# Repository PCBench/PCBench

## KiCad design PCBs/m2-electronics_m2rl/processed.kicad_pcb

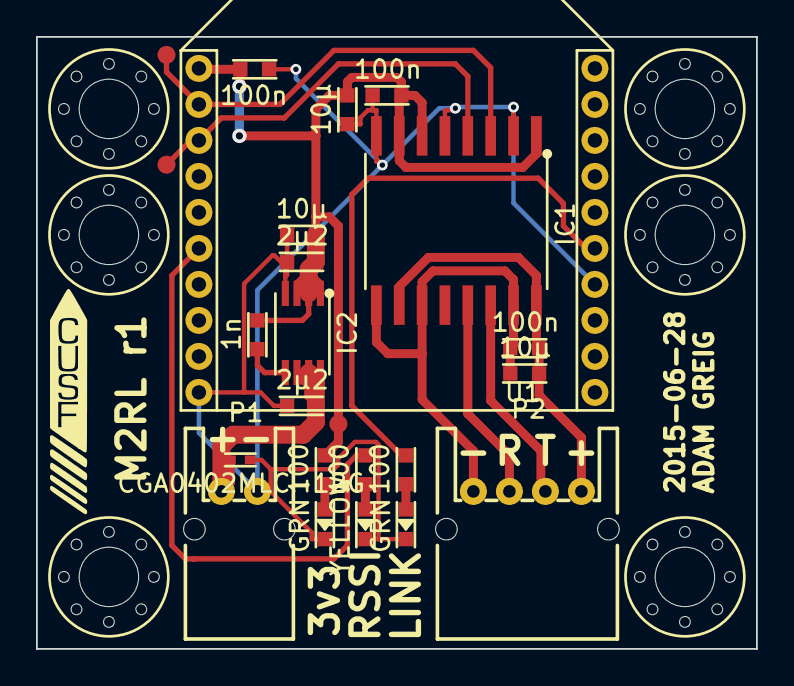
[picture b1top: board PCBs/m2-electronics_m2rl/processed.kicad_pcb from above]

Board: 2 copper layers, 40.0 x 34.0 mm, 30 parts (0 on the bottom side), 15 nets.

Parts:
C1, C7, C9: 10µ; C0603
C2, C3, C5: 100n; C0603
C4, C8: 2µ2; C0603
C6: 1n; C0603
D1: YELLOW; LED0603
D2: CGA0402MLC-12G; R0402
D3, D4: GRN; LED0603
IC1: ADuM5201; SOIC16W
IC2: ADP3335; MSOP8
M3_MOUNT, M3_MOUNT_2, M3_MOUNT_3, M3_MOUNT_4, M3_MOUNT_5, M3_MOUNT_6: VAL**; M3_MOUNT
P1: CONN_01X02; S02B-PASK-2
P2: CONN_01X04; S04B-PASK-2
R1, R2, R3: 100; R0603
TP3, TP4, TP5: TESTPAD
U1: XBEE

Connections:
+3V3: C1.1, C2.1, C3.1, C6.1, C8.1, C9.1, IC1.1, IC1.6, IC1.7, IC2.1, IC2.2, IC2.3, R3.1, TP5.1, U1.1
/DIN: IC1.4, TP4.1, U1.3
/DOUT: IC1.3, TP3.1, U1.2
GND: C1.2, C2.2, C3.2, C4.2, C8.2, C9.2, D1.1, D2.2, D3.1, D4.1, IC1.2, IC1.5, IC1.8, IC2.4, P1.1, U1.10, U1.14
unnamed: C4.1, D2.1, IC2.6, IC2.7, IC2.8, P1.2
unnamed: C5.1, C7.1, IC1.10, IC1.16, P2.1
unnamed: C5.2, C7.2, IC1.9, IC1.11, IC1.15, P2.4
unnamed: C6.2, IC2.5
unnamed: D1.2, R1.2
unnamed: D3.2, R2.2
unnamed: D4.2, R3.2
unnamed: IC1.13, P2.3
unnamed: IC1.14, P2.2
unnamed: R1.1, U1.6
unnamed: R2.1, U1.15

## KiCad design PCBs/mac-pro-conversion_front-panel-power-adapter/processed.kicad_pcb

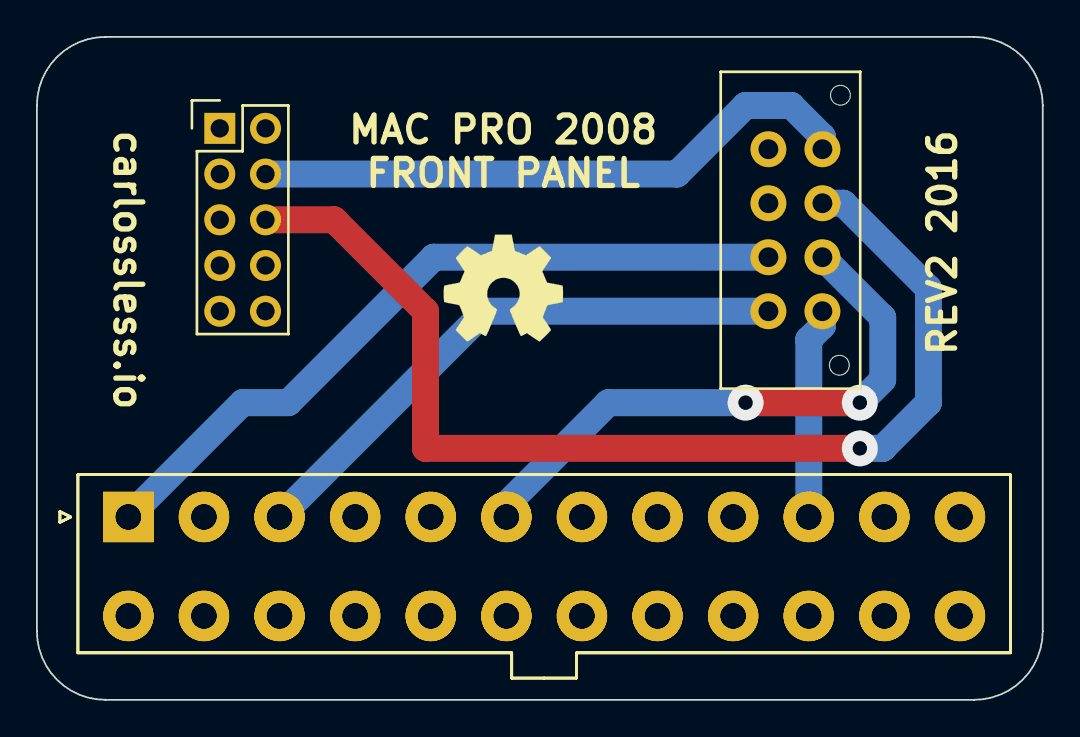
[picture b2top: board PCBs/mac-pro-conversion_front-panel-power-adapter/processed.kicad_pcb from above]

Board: 2 copper layers, 55.9 x 36.8 mm, 4 parts (0 on the bottom side), 26 nets.

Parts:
P3: CONN_02X04; Molex_Microfit3_Header_02x04_Straight_43045-0828
P4: CONN_02X05; Pin_Header_Straight_2x05
P7, P8: CONN_02X12; Molex_MiniFit-JR-5556-24A_2x12x4.20mm_Straight

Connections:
ATX01_3.3V: P3.2, P7.1, P8.1
ATX02: P7.2, P8.2
ATX04: P7.4, P8.4
ATX06_5V: P3.6, P7.6, P8.6
ATX08: P7.8, P8.8
ATX10_12V: P3.5, P7.10, P8.10
ATX12: P7.12, P8.12
ATX14: P7.14, P8.14
ATX16: P7.16, P8.16
ATX18: P7.18, P8.18
ATX20: P7.20, P8.20
ATX22: P7.22, P8.22
ATX24: P7.24, P8.24
ATX_05: P7.5, P8.5
ATX_07: P7.7, P8.7
ATX_09: P7.9, P8.9
ATX_11: P7.11, P8.11
ATX_13: P7.13, P8.13
ATX_15: P7.15, P8.15
ATX_17: P7.17, P8.17
ATX_19: P7.19, P8.19
ATX_21: P7.21, P8.21
ATX_23: P7.23, P8.23
GND: P3.1, P7.3, P8.3
MB_MSG-: P3.8, P4.4
MB_PW+: P3.7, P4.6

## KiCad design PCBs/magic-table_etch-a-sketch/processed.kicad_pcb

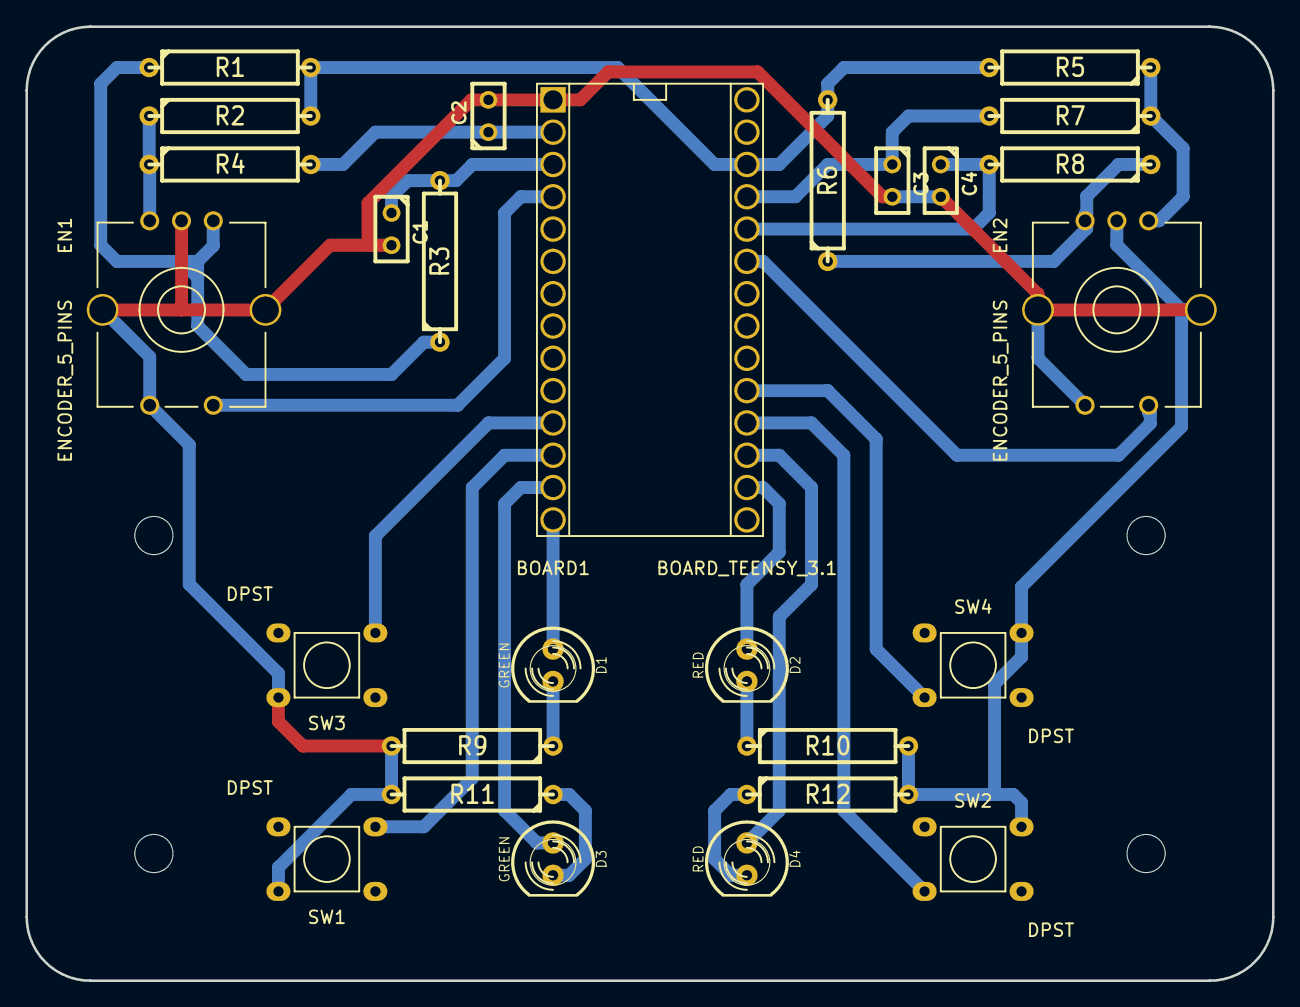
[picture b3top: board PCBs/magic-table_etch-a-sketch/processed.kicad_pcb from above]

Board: 2 copper layers, 98.0 x 75.0 mm, 31 parts (0 on the bottom side), 24 nets.

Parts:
BOARD1: BOARD_TEENSY_3.1; Board_Teensy_3_1
C1, C2, C3, C4: C; C1
D1, D3: GREEN; LED-5MM
D2, D4: RED; LED-5MM
EN1, EN2: ENCODER_5_PINS; Misc_Encoder_5_Pins_w_shield
Mechanical_drill_3mm, Mechanical_drill_3mm_2, Mechanical_drill_3mm_3, Mechanical_drill_3mm_4: Mechanical_drill_3mm
R1, R2, R3, R4, R5, R6, R7, R8, R9, R10, R11, R12: R; R5
SW1, SW2, SW3, SW4: DPST; Switches-Push_switch_THD

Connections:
/D0: BOARD1.2, C2.1, R4.2
/D1: BOARD1.3, C1.1, R3.2
/D2: BOARD1.4, EN1.4
/D9: BOARD1.11, SW3.3
/D10: BOARD1.12, SW1.3
/D11: BOARD1.13, D3.1
/D12: BOARD1.14, D1.1
/D14: BOARD1.16, D2.1
/D15: BOARD1.17, D4.1
/D16: BOARD1.18, SW2.3
/D17: BOARD1.19, SW4.3
/D21: BOARD1.23, EN2.4
/D22: BOARD1.24, C4.1, R8.2
/D23: BOARD1.25, C3.1, R7.2
GND: BOARD1.1, C1.2, C2.2, C3.2, C4.2, EN1.2, EN1.5, EN1.SHLD, EN2.2, EN2.5, EN2.SHLD, R9.2, R10.2, R11.2, R12.2, SW1.2, SW2.2, SW3.2, SW4.2
unnamed: D2.2, R10.1
unnamed: D4.2, R12.1
unnamed: D3.2, R11.1
unnamed: D1.2, R9.1
unnamed: EN2.1, R5.1, R7.1
unnamed: EN1.1, R1.1, R3.1
unnamed: EN1.3, R2.1, R4.1
unnamed: EN2.3, R6.1, R8.1
VCC: BOARD1.26, R1.2, R2.2, R5.2, R6.2

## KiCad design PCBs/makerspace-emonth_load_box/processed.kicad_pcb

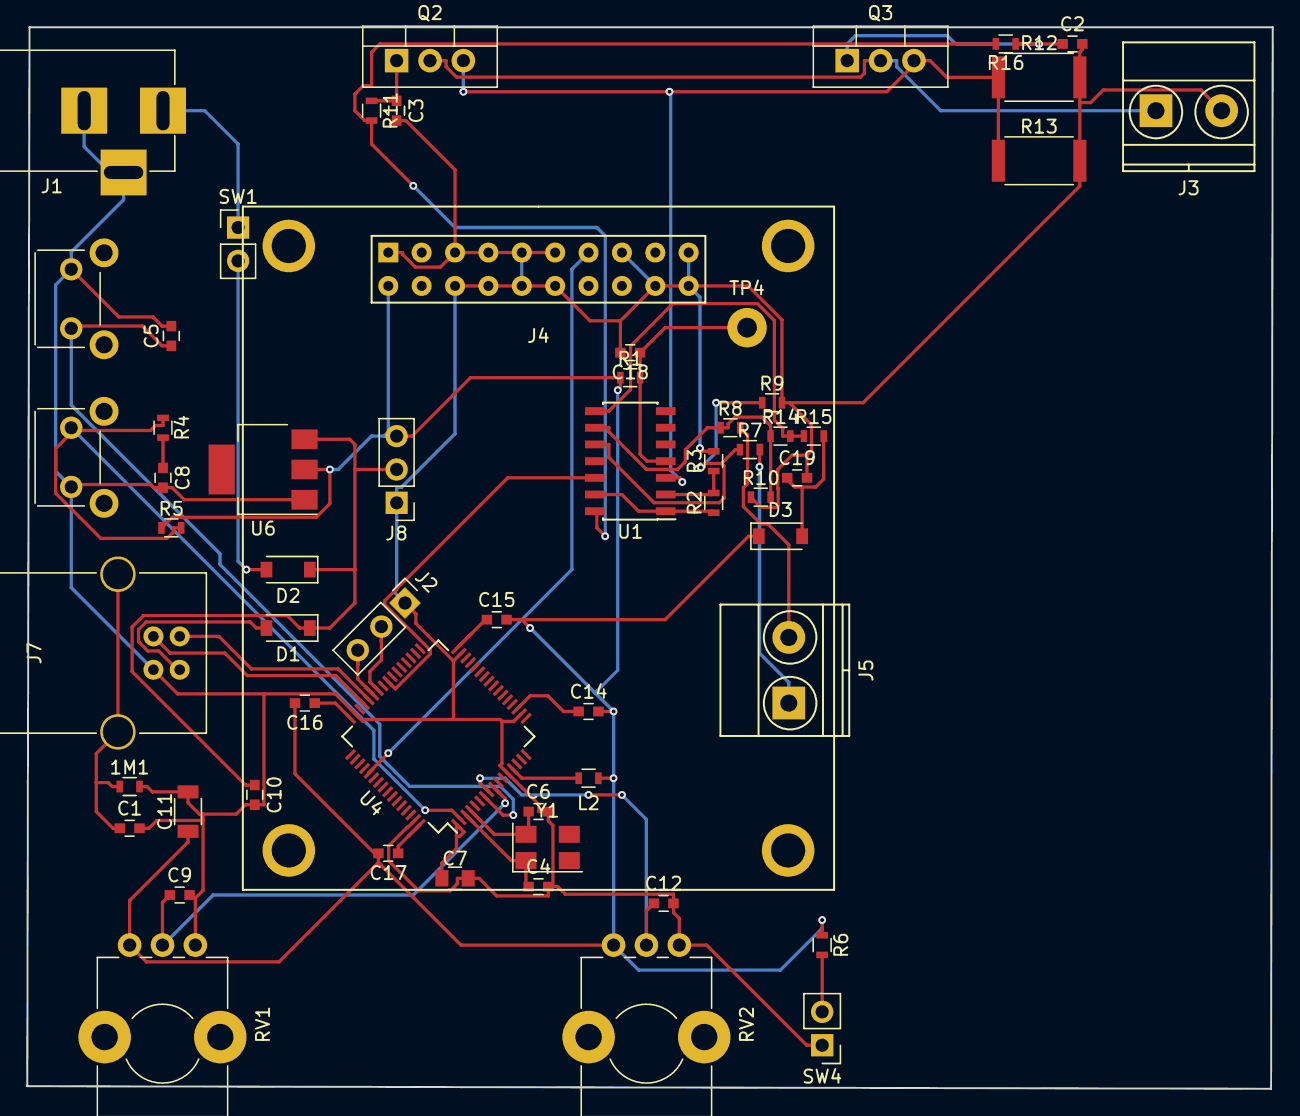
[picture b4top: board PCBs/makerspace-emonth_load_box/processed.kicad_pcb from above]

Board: 2 copper layers, 94.8 x 80.8 mm, 59 parts (0 on the bottom side), 41 nets.

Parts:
1M1: R; R_0603
C1: 4n7; C_0603
C2, C3, C5, C8, C9, C12, C18: 0.1; C_0603
C4, C6, C14, C15, C16, C17: C; C_0603
C7: 1.0; C_0805
C10: 0.1u; C_0603
C11: 10u; C_1206
C19: 4.7n; C_0603
D1, D2: D; D_SOD-123
D3: D_Schottky; D_SOD-123
J1: BARREL_JACK
J2, J8: CONN_01X03; Socket_Strip_Straight_1x03_Pitch2.54mm
J3, J5: Screw_Terminal_1x02; TerminalBlock_Pheonix_MKDS1.5-2pol
J4: CONN_02X10; NHD-1.69
J7: USB_B
L2: Ferrite_Bead; L_0603
Q2, Q3: FQP30N06L; TO-220_Vertical
R1, R4, R11, R16: 100R; R_0603
R2: 24K; R_0603
R3, R6, R9, R14: 10K; R_0603
R5, R10: 4.7K; R_0603
R7, R8, R15: 100K; R_0603
R12, R13: 0R1; R_2512
RV1, RV2: POT; Potentiometer_Alps_RK09K_Horizontal
SW1: SW_SPST; Socket_Strip_Straight_1x02_Pitch2.54mm
SW2, SW3: SW_Push; SW_Tactile_SKHH_Angled
SW4: SW_Push; Pin_Header_Straight_1x02_Pitch2.54mm
TP4: TEST; Measurement_Point_Round-TH_Big
U1: LM324; SOIC-14_3.9x8.7mm_Pitch1.27mm
U4: STM32L152RCTx; LQFP-64_10x10mm_Pitch0.5mm
U6: LD1117S33TR; SOT-223
Y1: Crystal_GND23; Crystal_SMD_5032-4pin_5.0x3.2mm

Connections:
+3V3: C11.1, C14.2, C15.2, C16.2, C17.2, D3.1, J4.2, J8.3, L2.1, R1.1, R5.1, R6.1, RV1.1, RV2.1, U6.2
+12V: D2.2, SW1.2
+BATT: C10.1, D1.1, D2.1, J8.2, U6.3
/load_box_display/MOSI: J4.13, U4.53
/load_box_interface/GO_BUTTON: R6.2, SW4.2
/load_box_interface/STATIC_VREF: C12.1, RV2.2, U4.8
/load_box_interface/STEP_VREF: C9.1, RV1.2, U4.9
/load_box_interface/USER_BUTTON: R4.1, R5.2, SW3.1, U4.2
/load_box_mcu/CHOSEN_VREF: U1.12, U4.40
/load_box_mcu/USB_DM: J7.2, U4.44
/load_box_mcu/USB_DP: J7.3, U4.45
/load_box_sink/REMOTE_SENSE_OUT: C19.1, D3.2, R15.2
GND: 1M1.2, C1.2, C2.2, C3.2, C4.2, C5.2, C6.2, C7.2, C8.2, C9.2, C10.2, C11.2, C12.2, C18.2, C19.2, J1.2, J1.3, J2.1, J3.2, J4.1, J4.5, J4.6, J4.7, J4.8, J4.9, J4.10, J4.11, J4.12, J4.15, J4.18, J4.19, J4.20, J7.4, J8.1, R3.2, R9.2, R10.1, R12.2, R13.2, RV1.3, RV2.3, SW2.1, SW3.2, SW4.1, U4.12, U4.18, U4.31, U4.47, U4.63, U6.1
NRST: C5.1, SW2.2, U4.7
unnamed: 1M1.1, C1.1, J7.5
unnamed: C2.1, Q3.1, R16.1
unnamed: C3.1, Q2.1, R11.1
unnamed: C4.1, U4.3, Y1.1
unnamed: C6.1, U4.4, Y1.4
unnamed: C7.1, U4.1
unnamed: C8.1, R4.2
unnamed: C14.1, U4.19
unnamed: C15.1, U4.32
unnamed: C16.1, U4.48
unnamed: C17.1, U4.64
unnamed: C18.1, R1.2, TP4.1, U1.4
unnamed: D1.2, J7.1
unnamed: J1.1, SW1.1
unnamed: J2.2, U4.42
unnamed: J2.3, U4.43
unnamed: J3.1, Q2.2, Q3.2
unnamed: J5.1, R7.2
unnamed: J5.2, R8.2
unnamed: L2.2, U4.13
unnamed: Q2.3, Q3.3, R12.1, R13.1, U1.3
unnamed: R2.1, U1.1, U1.13
unnamed: R2.2, R3.1, U1.2
unnamed: R7.1, R9.1, U1.10
unnamed: R8.1, R10.2, R14.1, U1.9
unnamed: R11.2, R16.2, U1.14
unnamed: R14.2, R15.1, U1.8
